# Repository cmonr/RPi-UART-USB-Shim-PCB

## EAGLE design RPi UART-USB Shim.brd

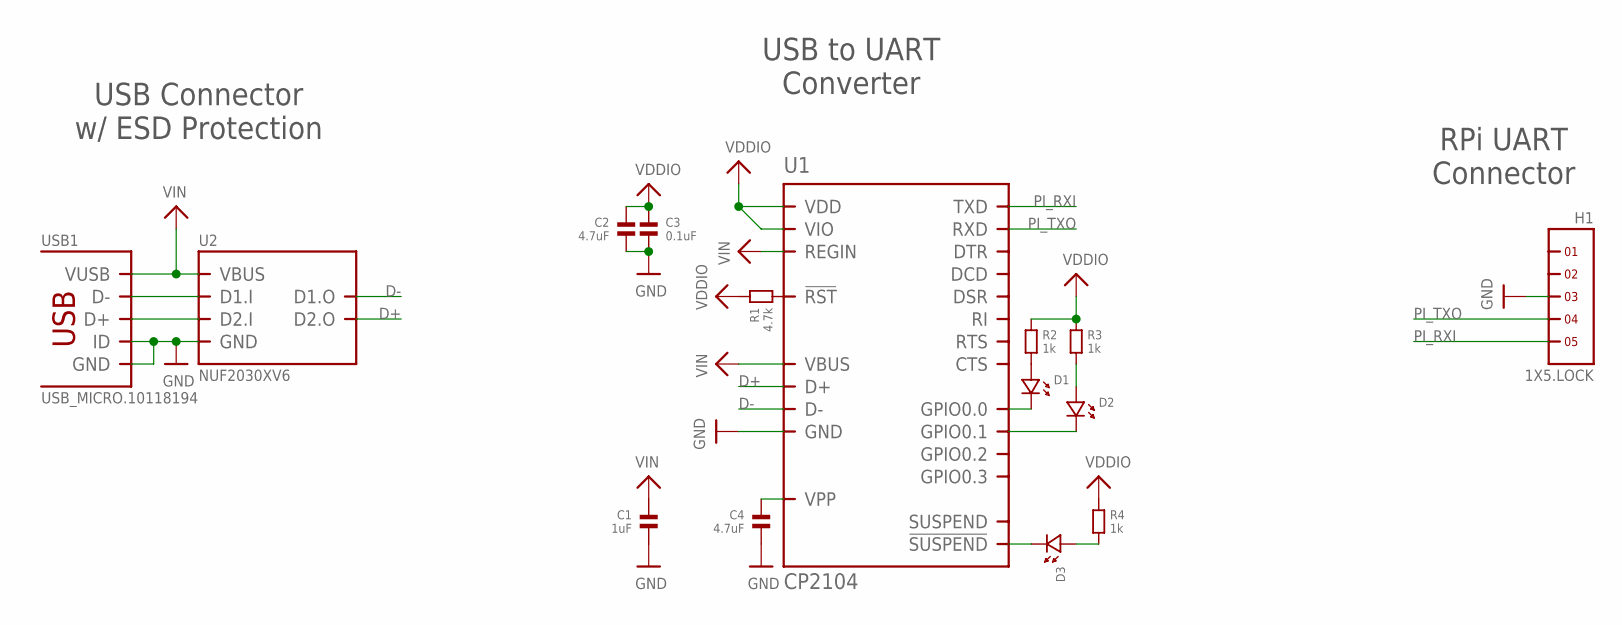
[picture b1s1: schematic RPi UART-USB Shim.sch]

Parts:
C1: 1uF; 0402
C2, C4: 4.7uF; 0402
C3: 0.1uF; 0402
D1, D2, D3: LED.0402; 0402.LED
H1: 1X5.LOCK
R1: 4.7k; 0402
R2, R3, R4: 1k; 0402
U1: CP2104; QFN24
U2: NUF2030XV6; SOT-563
USB1: USB_MICRO.10118194; 10118194

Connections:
D+: U1.3 (D+), U2.4 (D2.O)
D+.RAW: U2.3 (D2.I), USB1.3 (D+)
D-: U1.4 (D-), U2.6 (D1.O)
D-.RAW: U2.1 (D1.I), USB1.2 (D-)
GND: C1.2, C2.2, C3.2, C4.2, H1.3, U1.2 (GND), U1.PAD (GND), U2.2 (GND), USB1.4 (ID), USB1.5 (GND), USB1.PAD@1 (GND), USB1.PAD@2 (GND), USB1.PAD@3 (GND), USB1.PAD@4 (GND), USB1.PAD@5 (GND), USB1.PAD@6 (GND), USB1.PAD@7 (GND), USB1.PAD@8 (GND), USB1.PAD@9 (GND), USB1.PAD@10 (GND), USB1.PAD@11 (GND), USB1.PAD@12 (GND), USB1.PAD@13 (GND), USB1.PAD@14 (GND), USB1.PAD@15 (GND), USB1.PAD@16 (GND)
unnamed: C4.1, U1.16 (VPP)
unnamed: R1.2, U1.9 (!RST)
unnamed: D1.P$1 (1), R2.2
unnamed: D1.P$2 (2), U1.14 (GPIO0.0)
unnamed: D2.P$2 (2), U1.13 (GPIO0.1)
unnamed: D2.P$1 (1), R3.2
unnamed: D3.P$1 (1), R4.2
unnamed: D3.P$2 (2), U1.15 (!SUSPEND)
PI_RXI: H1.5, U1.21 (TXD)
PI_TXO: H1.4, U1.20 (RXD)
VDDIO: C2.1, C3.1, R1.1, R2.1, R3.1, R4.1, U1.5 (VIO), U1.6 (VDD)
VIN: C1.1, U1.7 (REGIN), U1.8 (VBUS), U2.5 (VBUS), USB1.1 (VUSB)

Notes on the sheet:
USB Connector w/ ESD Protection
USB to UART Converter
RPi UART Connector

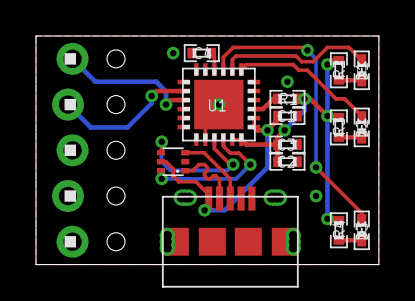
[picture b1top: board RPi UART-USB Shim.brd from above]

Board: 2 copper layers, 19.1 x 12.7 mm, 15 parts (0 on the bottom side), 17 nets.

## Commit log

2015-11-26 Initial commit. Components placed, schematic mostly complete (still needs ESD diodes)
2015-11-26 Added generated preview images
2015-11-26 Completed board layout and clenaed up schematic
2015-11-26 Regenerated file previews

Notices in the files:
parts and their libraries:
microbuilder: This work is placed in the public domain, and may be freely used for commercial and non-commercial work with the following conditions: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
